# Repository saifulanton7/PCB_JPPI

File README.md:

# Progress PCB JPPI

# Rules 
   1. Untuk Setiap Pembaruan desain pcb atau skematik harus di list log pengerjaan terakhir, Nama, tanggal dan jam, serta upload ulang file yg dikerjakan
   2. Untuk melanjutkan skematik, anda bisa lihat rangkaian pada rangkaian.pdf di github ini
   3. Kalau misalnya ada kesulitan pembacaan angka gambar, spek komponen atau jalur yang aneh, bisa dilist dan kalau memungkinkan kirimkan gambar

# Log Pengerjaan
1. Saiful Anton - 12 April 2021 (22:51 WIB)
   - Selesai mengerjakan Rangkaian Power Supply dan memcicil rangkaian isolation circuit
2. Saiful Anton - 14 April 2021 (22:29 WIB)
   - Selesai mengerjakan Rangkaian Isolation circuit dengan catatan Trafo/induktor tidak tau spek sehingga dikosongin
   - Mencicil skematik forward direction gate controller
   - file skematik sudah diupdate
3. Saiful Anton - 15 April 2021 (22:45 WIB)
   - Selesai mengerjakan Rangkaian forward directional gate controller dengan catatan Trafo/induktor tidak tau spesifikasinya dan diganti dengan komponen eagle yang lain
   - file skematik sudah diupdate
3. Saiful Anton - 26 April 2021 (12:07 WIB)
   - Selesai mengerjakan Rangkaian logic circuit dan reverse directional gate controller
   - file skematik sudah diupdate
   
# Log Kesulitan
1. Saiful Anton - 12 April 2021 (22:51 WIB)
   - Kesulitan Library Trafo Power CT 18VAC, dan Trafo Power CT 9VAC pada rangkaian  
   - Tidak Tahu Spek Trafo dirangkaian isolation circuit
   - Tidak Jelasnya Nilai Resitor didekat Transistor TR1 Sampai TR8
2. Saiful Anton - 14 April 2021 (22:29 WIB)
   - Kesulitan Library Trafo/induktor tidak ada dan saya tidak tahu jenis dan speknya  
3. Saiful Anton - 15 April 2021 (22:45 WIB)
   - tidak tahunya spesifikasi Trafo/induktor isolasi

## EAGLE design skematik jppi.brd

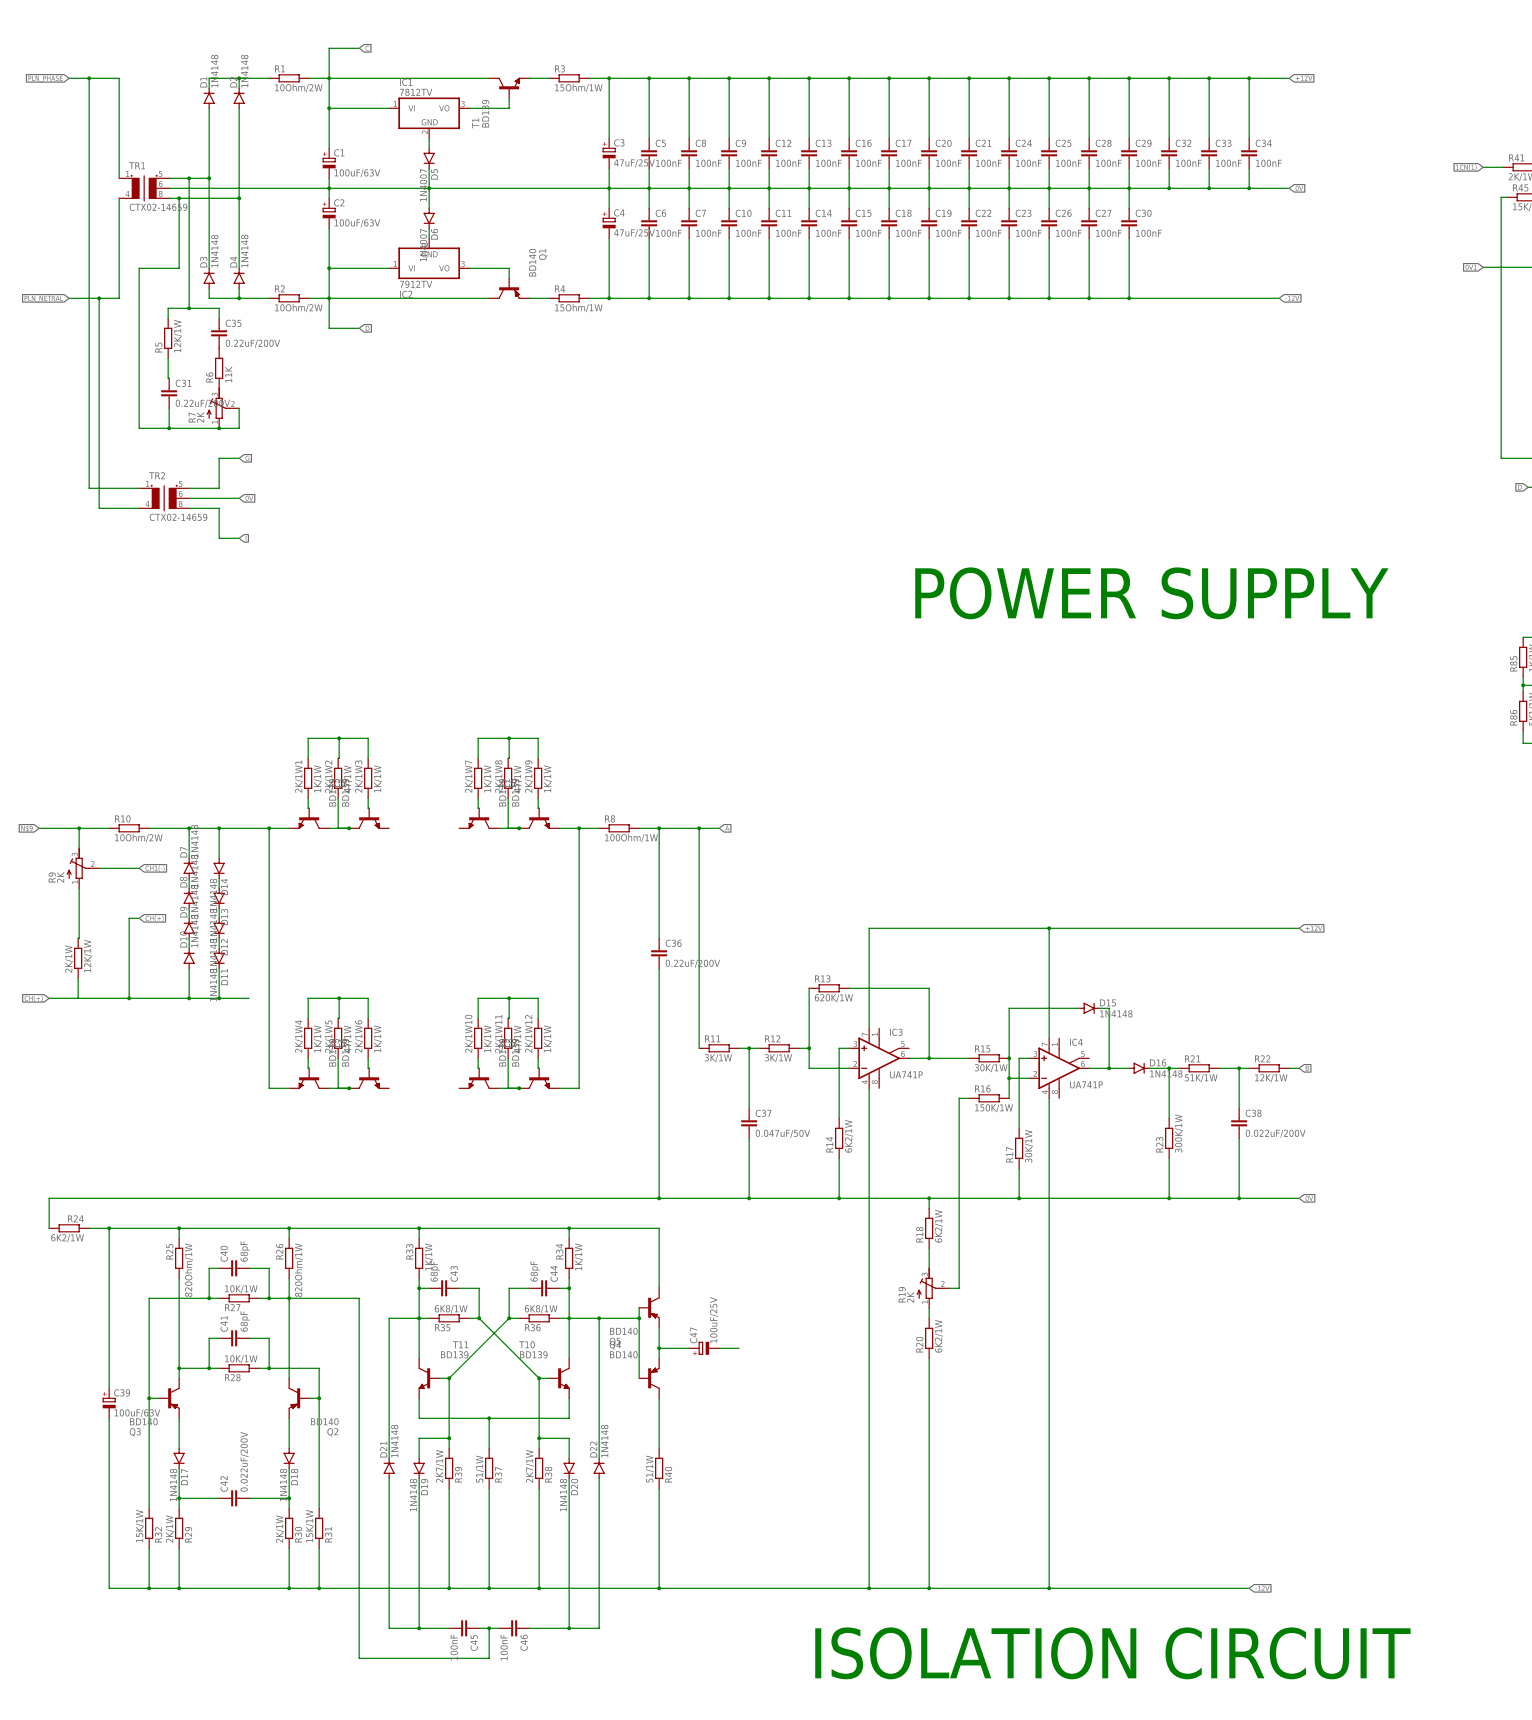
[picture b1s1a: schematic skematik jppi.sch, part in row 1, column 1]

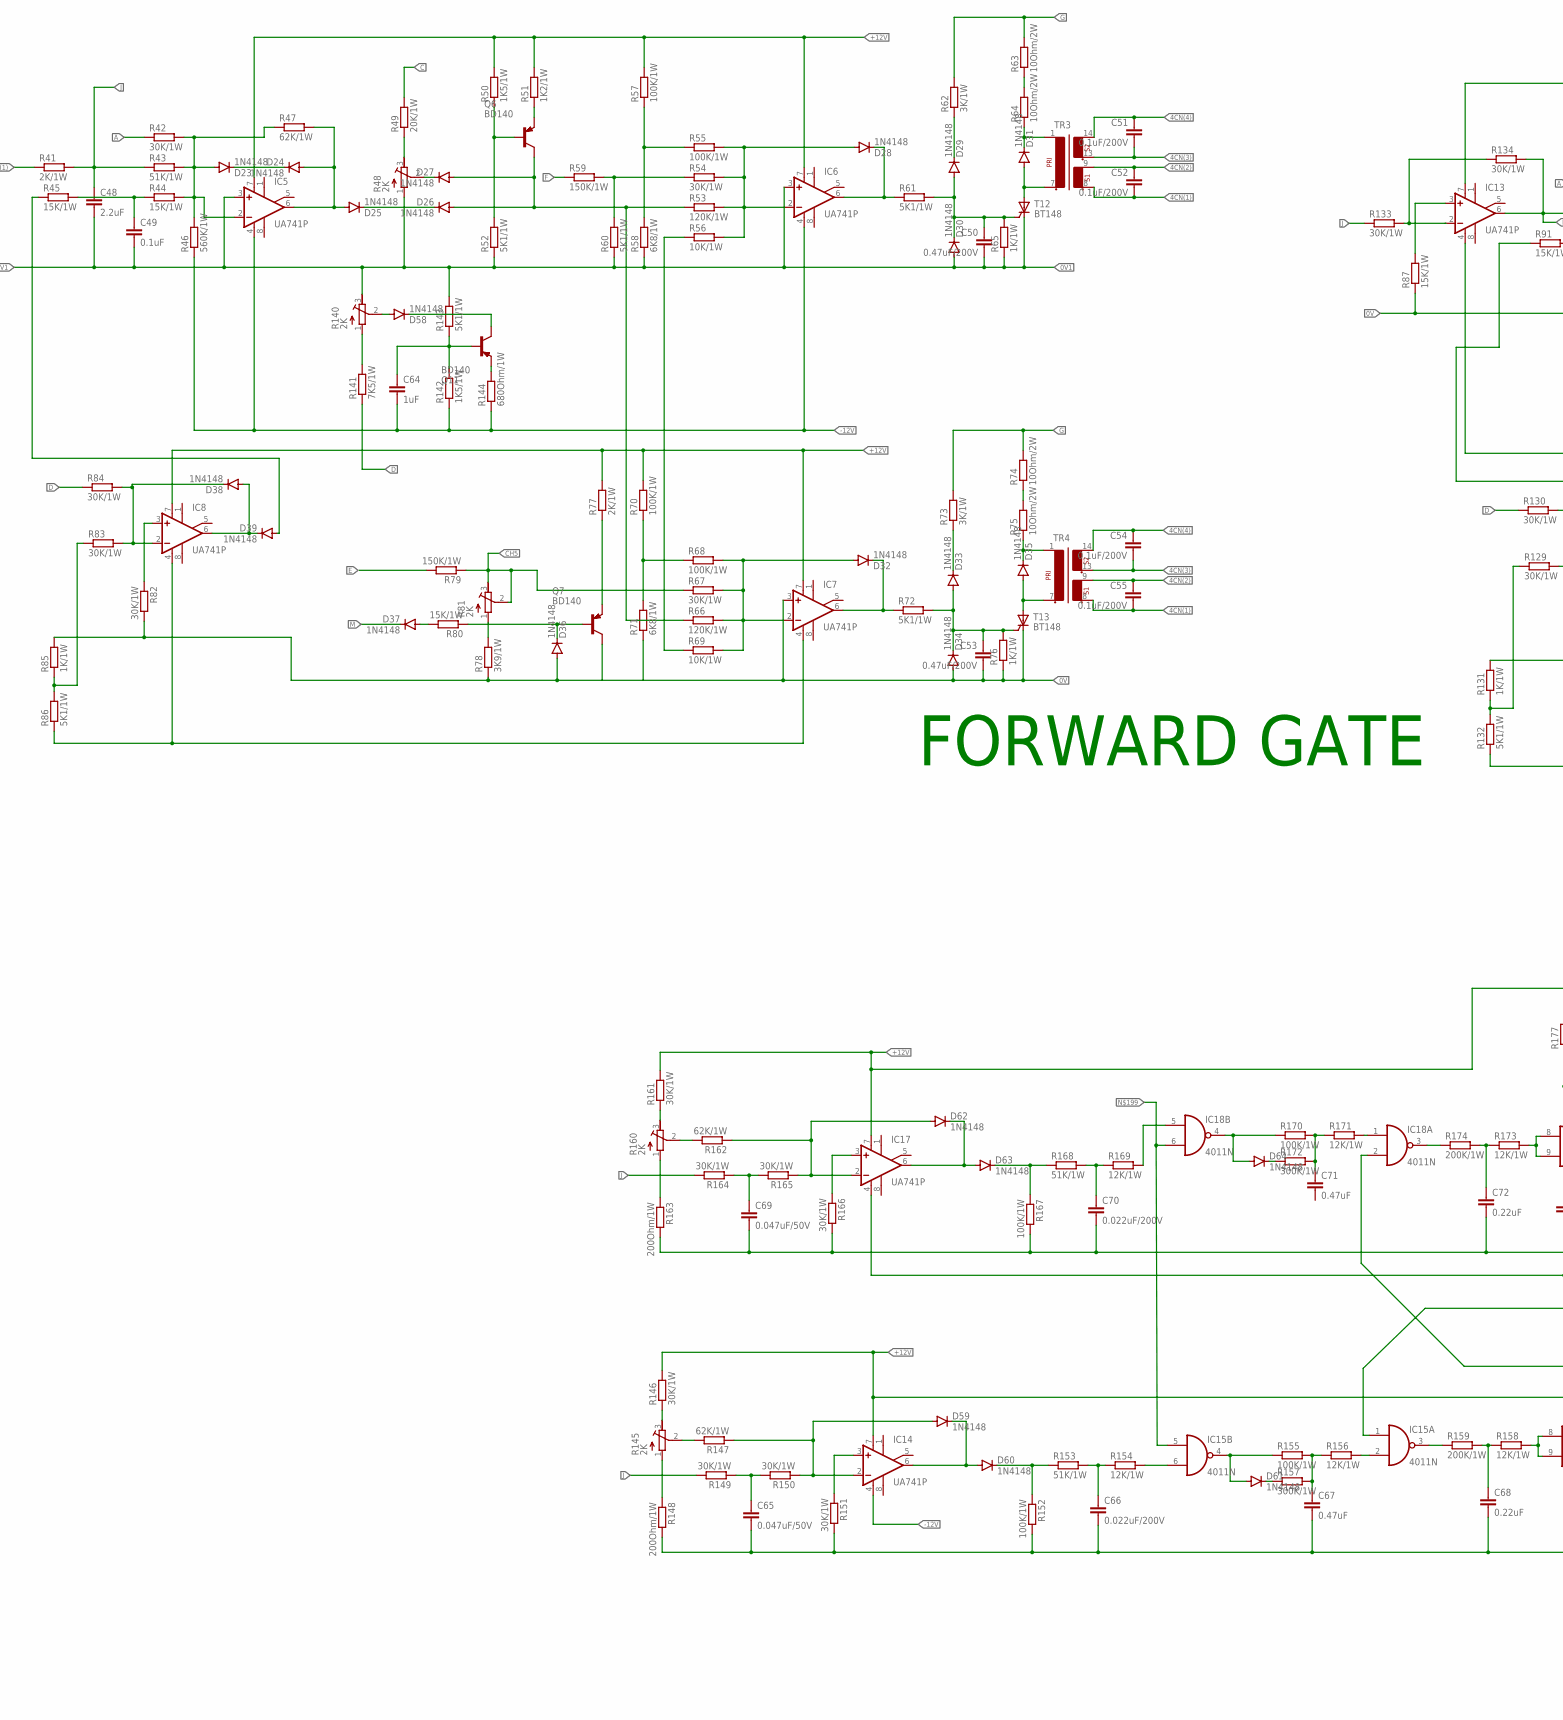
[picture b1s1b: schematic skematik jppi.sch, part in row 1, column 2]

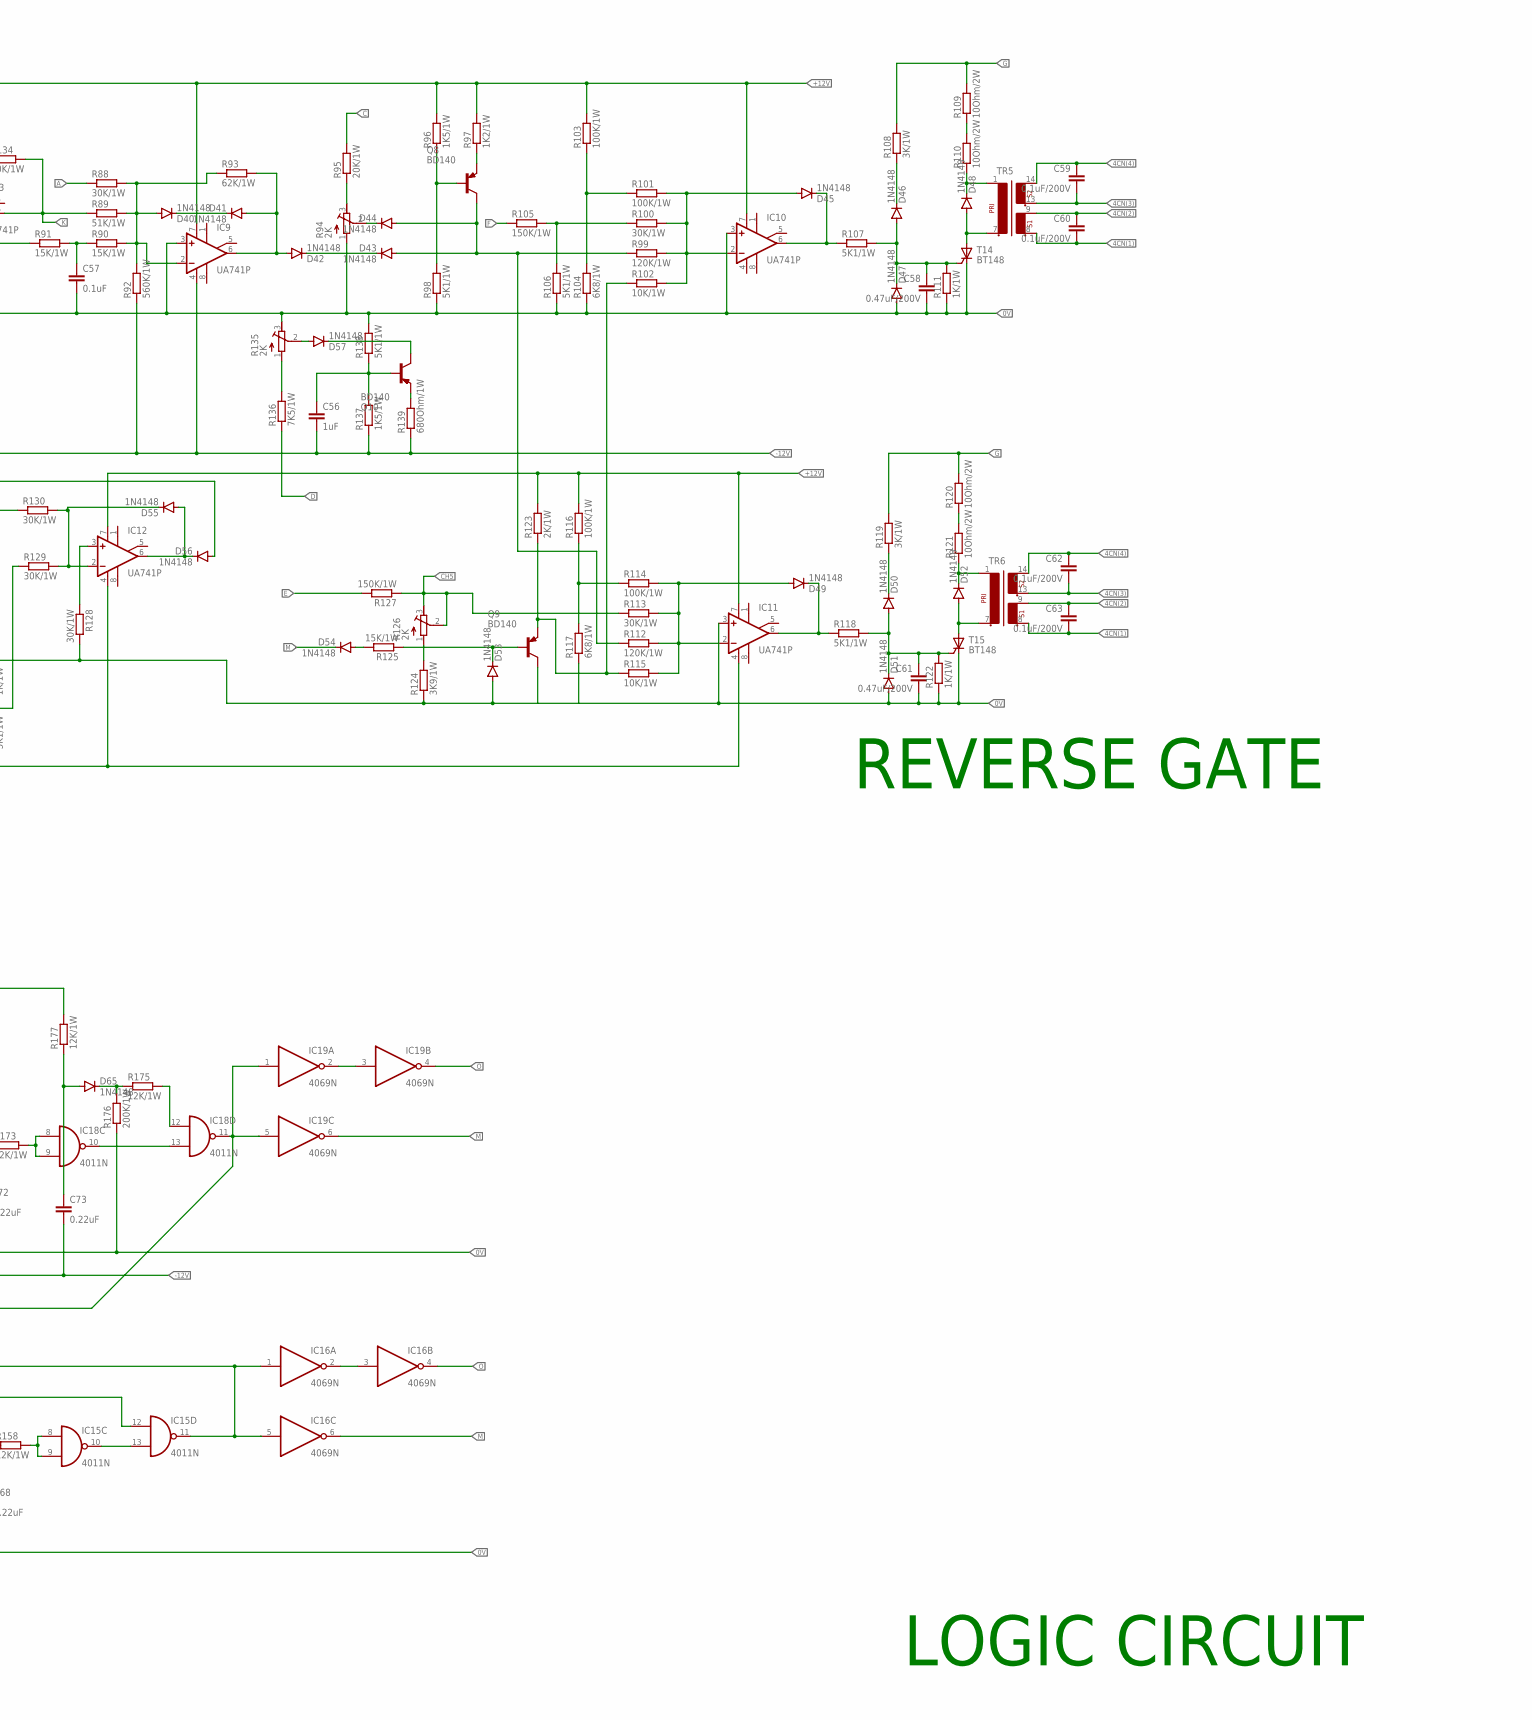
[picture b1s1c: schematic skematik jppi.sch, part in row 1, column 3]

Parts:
2K/1W: 12K/1W; 0309/12
2K/1W1, 2K/1W3, 2K/1W4, 2K/1W6, 2K/1W7, 2K/1W9, 2K/1W10, 2K/1W12: 1K/1W; 0309/12
2K/1W2, 2K/1W5, 2K/1W8, 2K/1W11: 47/1W; 0309/12
C1, C2, C39: 100uF/63V; E5-10,5
C3, C4: 47uF/25V; E5-10,5
C5, C6, C7, C8, C9, C10, C11, C12, C13, C14, C15, C16, C17, C18, C19, C20, C21, C22, C23, C24, C25, C26, C27, C28, C29, C30, C32, C33, C34, C45, C46: 100nF; C050-025X075
C31, C35, C36: 0.22uF/200V; C102-043X133
C37: 0.047uF/50V; C075-032X103
C38, C42, C66, C70: 0.022uF/200V; C102-043X133
C40, C41, C43, C44: 68pF; C050-024X044
C47: 100uF/25V; E5-10,5
C48: 2.2uF; C050-025X075
C49, C57: 0.1uF; C050-025X075
C50, C53, C58, C61: 0.47uF/200V; C102-043X133
C51, C52, C54, C55, C59, C60, C62, C63: 0.1uF/200V; C102-043X133
C56, C64: 1uF; C050-025X075
C65, C69: 0.047uF/50V; C102-043X133
C67, C71: 0.47uF; C102-043X133
C68, C72, C73: 0.22uF; C102-043X133
D1, D2, D3, D4, D7, D8, D9, D10, D11, D12, D13, D14, D15, D16, D17, D18, D19, D20, D21, D22, D23, D24, D25, D26, D27, D28, D29, D30, D31, D32, D33, D34, D35, D36, D37, D38, D39, D40, D41, D42, D43, D44, D45, D46, D47, D48, D49, D50, D51, D52, D53, D54, D55, D56, D57, D58, D59, D60, D61, D62, D63, D64, D65: 1N4148; DO41-10
D5, D6: 1N4007; DO41-10
IC1: 7812TV; TO220V
IC2: 7912TV; TO220V
IC3, IC4, IC5, IC6, IC7, IC8, IC9, IC10, IC11, IC12, IC13, IC14, IC17: UA741P; DIL08
IC15, IC18: 4011N; DIL14
IC16, IC19: 4069N; DIL14
Q1, Q2, Q3, Q4, Q5, Q6, Q7, Q8, Q9, Q10, Q11: BD140; TO126
R1, R2, R10, R63, R64, R74, R75, R109, R110, R120, R121: 10Ohm/2W; 0411/15
R3, R4: 15Ohm/1W; 0309/12
R5: 12K/1W; 0309/12
R6: 11K; 0309/12
R7, R9, R19, R48, R81, R94, R126, R135, R140, R145, R160: 2K; RTRIM3339P
R8: 100Ohm/1W; 0411/15
R11, R12, R62, R73, R108, R119: 3K/1W; 0411/15
R13: 620K/1W; 0411/15
R14, R18, R20, R24: 6K2/1W; 0411/15
R15, R17, R42, R54, R67, R82, R83, R84, R88, R100, R113, R128, R129, R130, R133, R134, R146, R149, R150, R151, R161, R164, R165, R166: 30K/1W; 0411/15
R16, R59, R79, R105, R127: 150K/1W; 0411/15
R21, R43, R89, R153, R168: 51K/1W; 0411/15
R22, R154, R156, R158, R169, R171, R173, R175, R177: 12K/1W; 0411/15
R23, R157, R172: 300K/1W; 0411/15
R25, R26: 820Ohm/1W; 0411/15
R27, R28, R56, R69, R102, R115: 10K/1W; 0411/15
R29, R30, R41, R77, R123: 2K/1W; 0411/15
R31, R32, R44, R45, R80, R87, R90, R91, R125: 15K/1W; 0411/15
R33, R34, R65, R76, R85, R111, R122, R131: 1K/1W; 0411/15
R35, R36, R58, R71, R104, R117: 6K8/1W; 0411/15
R37, R40: 51/1W; 0411/15
R38, R39: 2K7/1W; 0411/15
R46, R92: 560K/1W; 0411/15
R47, R93, R147, R162: 62K/1W; 0411/15
R49, R95: 20K/1W; 0411/15
R50, R96, R137, R142: 1K5/1W; 0411/15
R51, R97: 1K2/1W; 0411/15
R52, R60, R61, R72, R86, R98, R106, R107, R118, R132, R138, R143: 5K1/1W; 0411/15
R53, R66, R99, R112: 120K/1W; 0411/15
R55, R57, R68, R70, R101, R103, R114, R116, R152, R155, R167, R170: 100K/1W; 0411/15
R78, R124: 3K9/1W; 0411/15
R136, R141: 7K5/1W; 0411/15
R139, R144: 680Ohm/1W; 0411/15
R148, R163: 200Ohm/1W; 0411/15
R159, R174, R176: 200K/1W; 0411/15
T1, T2, T3, T4, T5, T6, T7, T8, T9, T10, T11: BD139; TO126
T12, T13, T14, T15: BT148; SOT82S
TR1, TR2: CTX02-14659
TR3, TR4, TR5, TR6: EI54-2

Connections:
0V: C1.-, C2.+, C3.-, C4.+, C5.2, C6.1, C7.1, C8.2, C9.2, C10.1, C11.1, C12.2, C13.2, C14.1, C15.1, C16.2, C17.2, C18.1, C19.1, C20.2, C21.2, C22.1, C23.1, C24.2, C25.2, C26.1, C27.1, C28.2, C29.2, C30.1, C32.2, C33.2, C34.2, C36.2, C37.2, C38.2, C53.2, C57.2, C58.2, C61.2, C65.2, C66.2, C67.2, C68.2, C69.2, C70.2, C72.2, D5.C, D6.A, D34.A, D36.A, D47.A, D51.A, D53.A, IC7.3 (+IN), IC9.3 (+IN), IC10.3 (+IN), IC11.3 (+IN), Q7.2 (C), Q9.2 (C), R14.1, R17.1, R18.2, R23.1, R24.2, R71.1, R76.1, R78.1, R82.2, R85.2, R87.1, R94.1 (A), R98.1, R104.1, R106.1, R111.1, R117.1, R122.1, R124.1, R128.2, R131.2, R135.3 (E), R138.2, R148.2, R151.2, R152.2, R163.2, R166.2, R167.2, R176.1, T13.C, T14.C, T15.C, TR1.6 (4), TR2.6 (4)
0V1: C48.2, C49.2, C50.2, D30.A, IC5.3 (+IN), IC6.3 (+IN), R48.1 (A), R52.1, R58.1, R60.1, R65.1, R140.3 (E), R143.2, T12.C
1CN(1): R41.1
4CN(1): C52.2, C55.2, C60.2, C63.2, TR3.8 (3), TR4.8 (3), TR5.8 (3), TR6.8 (3)
4CN(2): C52.1, C55.1, C60.1, C63.1, TR3.9 (4), TR4.9 (4), TR5.9 (4), TR6.9 (4)
4CN(3): C51.2, C54.2, C59.2, C62.2, TR3.13 (5), TR4.13 (5), TR5.13 (5), TR6.13 (5)
4CN(4): C51.1, C54.1, C59.1, C62.1, TR3.14 (6), TR4.14 (6), TR5.14 (6), TR6.14 (6)
+12V: C3.+, C5.1, C8.1, C9.1, C12.1, C13.1, C16.1, C17.1, C20.1, C21.1, C24.1, C25.1, C28.1, C29.1, C32.1, C33.1, C34.1, IC3.7 (V+), IC4.7 (V+), IC5.7 (V+), IC6.7 (V+), IC7.7 (V+), IC8.7 (V+), IC9.7 (V+), IC10.7 (V+), IC11.7 (V+), IC12.7 (V+), IC13.7 (V+), IC14.7 (V+), IC15.12 (I0), IC17.7 (V+), R3.2, R50.2, R51.2, R57.2, R70.2, R77.2, R96.2, R97.2, R103.2, R116.2, R123.2, R146.2, R161.2, R177.2
-12V: C4.-, C6.2, C7.2, C10.2, C11.2, C14.2, C15.2, C18.2, C19.2, C22.2, C23.2, C26.2, C27.2, C30.2, C39.-, C56.2, C64.2, C73.2, IC3.4 (V-), IC4.4 (V-), IC5.4 (V-), IC6.4 (V-), IC9.4 (V-), IC13.4 (V-), IC14.4 (V-), IC17.4 (V-), R4.2, R20.1, R29.1, R30.1, R31.1, R32.1, R37.1, R38.1, R39.1, R40.1, R46.1, R92.1, R137.1, R139.1, R142.1, R144.1
A: C36.1, R8.2, R11.1, R42.1, R88.1
B: R22.2
C: C1.+, IC1.1 (VI), R1.2, R49.2, R95.2, T1.2 (C)
CH1(-): R9.2 (S)
CH5: R67.1, R79.1, R81.2 (S), R81.3 (E), R113.1, R126.2 (S), R126.3 (E), R127.1
CH(+): 2K/1W.1, D10.A, D11.C
D: C2.-, IC2.1 (VI), Q1.2 (C), R2.2, R84.1, R130.1, R136.1, R141.1
E: R79.2, R127.2
F: R59.1, R105.1
G: R62.2, R63.2, R73.2, R74.2, R108.2, R109.2, R119.2, R120.2, TR2.5
I: TR2.8 (3)
J: C48.1, R41.2, R43.1, R133.1, R149.2, R164.2
K: IC13.6 (OUT), R89.1, R134.2
M: D37.C, D54.C, IC16.6 (O), IC19.6 (O)
unnamed: C35.1, D1.A, D3.C, R5.2, TR1.5
unnamed: C31.2, D2.A, D4.C, R7.1 (A), R7.2 (S), TR1.8 (3)
unnamed: D1.C, D2.C, R1.1
unnamed: D3.A, D4.A, R2.1
unnamed: R6.1, R7.3 (E)
unnamed: C31.1, R5.1
unnamed: 2K/1W.2, R9.1 (A)
unnamed: D6.C, IC2.2 (GND)
unnamed: R9.3 (E), R10.1
unnamed: D5.A, IC1.2 (GND)
unnamed: IC1.3 (VO), T1.3 (B)
unnamed: IC2.3 (VO), Q1.3 (B)
unnamed: Q1.1 (E), R4.1
unnamed: R3.1, T1.1 (E)
unnamed: D7.A, D8.C
unnamed: D7.C, D14.A, R10.2, T2.1 (E), T4.1 (E)
unnamed: 2K/1W2.1, T2.2 (C), T3.2 (C)
unnamed: C35.2, R6.2
unnamed: D8.A, D9.C
unnamed: D9.A, D10.C
unnamed: D11.A, D12.C
unnamed: D12.A, D13.C
unnamed: D13.A, D14.C
unnamed: 2K/1W1.1, T2.3 (B)
unnamed: 2K/1W3.1, T3.3 (B)
unnamed: 2K/1W1.2, 2K/1W2.2, 2K/1W3.2
unnamed: 2K/1W5.1, T4.2 (C), T5.2 (C)
unnamed: 2K/1W4.1, T4.3 (B)
unnamed: 2K/1W6.1, T5.3 (B)
unnamed: 2K/1W4.2, 2K/1W5.2, 2K/1W6.2
unnamed: 2K/1W8.1, T6.2 (C), T7.2 (C)
unnamed: 2K/1W7.1, T6.3 (B)
unnamed: 2K/1W9.1, T7.3 (B)
unnamed: 2K/1W7.2, 2K/1W8.2, 2K/1W9.2
unnamed: 2K/1W11.1, T8.2 (C), T9.2 (C)
unnamed: 2K/1W10.1, T8.3 (B)
unnamed: 2K/1W12.1, T9.3 (B)
unnamed: 2K/1W10.2, 2K/1W11.2, 2K/1W12.2
unnamed: R8.1, T7.1 (E), T9.1 (E)
unnamed: R63.1, R64.2
unnamed: R19.1 (A), R20.2
unnamed: C37.1, R11.2, R12.1
unnamed: IC3.2 (-IN), R12.2, R13.1
unnamed: IC3.6 (OUT), R13.2, R15.1
unnamed: IC3.3 (+IN), R14.2
unnamed: IC4.3 (+IN), R17.2
unnamed: R18.1, R19.3 (E)
unnamed: R16.1, R19.2 (S)
unnamed: D15.C, D16.A, IC4.6 (OUT)
unnamed: C39.+, Q5.2 (C), R24.1, R25.1, R26.1, R33.1, R34.1
unnamed: D16.C, R21.1, R23.2
unnamed: C38.1, R21.2, R22.1
unnamed: C41.1, Q3.2 (C), R25.2, R28.1
unnamed: C47.+, Q4.1 (E), Q5.1 (E)
unnamed: C41.2, Q2.3 (B), R28.2, R31.2
unnamed: C40.1, Q3.3 (B), R27.1, R32.2
unnamed: D17.A, Q3.1 (E)
unnamed: D18.A, Q2.1 (E)
unnamed: C42.1, D17.C, R29.2
unnamed: C42.2, D18.C, R30.2
unnamed: C43.2, D21.C, R33.2, R35.1, T11.2 (C)
unnamed: C40.2, C45.1, C46.2, Q2.2 (C), R26.2, R27.2
unnamed: C43.1, D20.A, R35.2, R38.2, T10.3 (B)
unnamed: C44.2, D19.A, R36.1, R39.2, T11.3 (B)
unnamed: R37.2, T10.1 (E), T11.1 (E)
unnamed: C46.1, D20.C, D22.A
unnamed: C44.1, D22.C, Q4.3 (B), Q5.3 (B), R34.2, R36.2, T10.2 (C)
unnamed: C45.2, D19.C, D21.A
unnamed: D23.A, IC5.2 (-IN), R42.2, R43.2, R44.2, R46.2, R47.1
unnamed: Q4.2 (C), R40.2
unnamed: C49.1, R44.1, R45.2
unnamed: R56.1, R69.1
unnamed: D15.A, IC4.2 (-IN), R15.2, R16.2
unnamed: D24.A, D25.A, IC5.6 (OUT), R47.2
unnamed: D25.C, D26.C
unnamed: D23.C, D24.C
unnamed: D27.C, R48.2 (S)
unnamed: R48.3 (E), R49.1
unnamed: Q6.1 (E), R51.1
unnamed: Q6.3 (B), R50.1, R52.2
unnamed: D26.A, D27.A, Q6.2 (C), R53.1, R66.1
unnamed: D28.A, IC6.2 (-IN), R53.2, R54.2, R55.2, R56.2
unnamed: R55.1, R57.1, R58.2
unnamed: R54.1, R59.2, R60.2
unnamed: D28.C, IC6.6 (OUT), R61.1
unnamed: C50.1, D29.A, D30.C, R61.2, R65.2, T12.G
unnamed: D29.C, R62.1
unnamed: D31.C, R64.1, TR3.1
unnamed: D31.A, T12.A, TR3.7 (2)
unnamed: D32.A, IC7.2 (-IN), R66.2, R67.2, R68.2, R69.2
unnamed: R68.1, R70.1, R71.2
unnamed: R78.2, R81.1 (A)
unnamed: D32.C, IC7.6 (OUT), R72.1
unnamed: C53.1, D33.A, D34.C, R72.2, R76.2, T13.G
unnamed: D33.C, R73.1
unnamed: R74.1, R75.2
unnamed: D35.C, R75.1, TR4.1
unnamed: D35.A, T13.A, TR4.7 (2)
unnamed: Q7.1 (E), R77.1
unnamed: D36.C, Q7.3 (B), R80.1
unnamed: IC7.4 (V-), IC8.4 (V-), R86.1
unnamed: R83.1, R85.1, R86.2
unnamed: D37.A, R80.2
unnamed: D38.A, D39.C, IC8.6 (OUT)
unnamed: IC8.3 (+IN), R82.1
unnamed: D38.C, IC8.2 (-IN), R83.2, R84.2
unnamed: D39.A, R45.1
unnamed: D40.A, IC9.2 (-IN), R88.2, R89.2, R90.2, R92.2, R93.1
unnamed: C57.1, R90.1, R91.2
unnamed: D41.A, D42.A, IC9.6 (OUT), R93.2
unnamed: D40.C, D41.C
unnamed: D42.C, D43.C
unnamed: D44.C, R94.2 (S)
unnamed: R94.3 (E), R95.1
unnamed: Q8.1 (E), R97.1
unnamed: Q8.3 (B), R96.1, R98.2
unnamed: D43.A, D44.A, Q8.2 (C), R99.1, R112.1
unnamed: D45.A, IC10.2 (-IN), R99.2, R100.2, R101.2, R102.2
unnamed: R101.1, R103.1, R104.2
unnamed: R100.1, R105.2, R106.2
unnamed: D45.C, IC10.6 (OUT), R107.1
unnamed: C58.1, D46.A, D47.C, R107.2, R111.2, T14.G
unnamed: D46.C, R108.1
unnamed: R109.1, R110.2
unnamed: D48.C, R110.1, TR5.1
unnamed: D48.A, T14.A, TR5.7 (2)
unnamed: D57.C, Q10.2 (C)
unnamed: C56.1, Q10.3 (B), R137.2, R138.1
unnamed: D49.A, IC11.2 (-IN), R112.2, R113.2, R114.2, R115.2
unnamed: R114.1, R116.1, R117.2
unnamed: D49.C, IC11.6 (OUT), R118.1
unnamed: C61.1, D50.A, D51.C, R118.2, R122.2, T15.G
unnamed: D50.C, R119.1
unnamed: R120.1, R121.2
unnamed: Q9.1 (E), R102.1, R115.1, R123.1
unnamed: D52.C, R121.1, TR6.1
unnamed: D52.A, T15.A, TR6.7 (2)
unnamed: D58.A, R140.2 (S)
unnamed: R124.2, R126.1 (A)
unnamed: D58.C, Q11.2 (C)
unnamed: D53.C, Q9.3 (B), R125.1
unnamed: D54.A, R125.2
unnamed: IC11.4 (V-), IC12.4 (V-), R132.1
unnamed: R129.1, R131.1, R132.2
unnamed: D55.A, D56.C, IC12.6 (OUT)
unnamed: D55.C, IC12.2 (-IN), R129.2, R130.2
unnamed: IC13.3 (+IN), R87.2
unnamed: IC13.2 (-IN), R133.2, R134.1
unnamed: D57.A, R135.2 (S)
unnamed: Q10.1 (E), R139.2
unnamed: IC12.3 (+IN), R128.1
unnamed: D56.A, R91.1
unnamed: C64.1, Q11.3 (B), R142.2, R143.1
unnamed: R135.1 (A), R136.2
unnamed: R140.1 (A), R141.2
unnamed: Q11.1 (E), R144.2
unnamed: R145.3 (E), R146.1
unnamed: R145.1 (A), R148.1
unnamed: R145.2 (S), R147.2
unnamed: C65.1, R149.1, R150.2
unnamed: R160.3 (E), R161.1
unnamed: D59.A, IC14.2 (-IN), R147.1, R150.1
unnamed: IC14.3 (+IN), R151.1
unnamed: D59.C, D60.A, IC14.6 (OUT)
unnamed: D60.C, R152.1, R153.1
unnamed: C66.1, R153.2, R154.1
unnamed: IC15.11 (O), IC16.1 (I), IC16.5 (I), IC18.2 (I1)
unnamed: IC16.2 (O), IC16.3 (I)
unnamed: IC15.6 (I1), R154.2
unnamed: R160.1 (A), R163.1
unnamed: IC15.10 (O), IC15.13 (I1)
unnamed: IC15.8 (I0), IC15.9 (I1), R158.2
unnamed: C67.1, R155.2, R156.1, R157.2
unnamed: D61.A, IC15.4 (O), R155.1
unnamed: D61.C, R157.1
unnamed: IC15.3 (O), R159.1
unnamed: C68.1, R158.1, R159.2
unnamed: IC15.2 (I1), R156.2
unnamed: R160.2 (S), R162.2
unnamed: C69.1, R164.1, R165.2
unnamed: D62.A, IC17.2 (-IN), R162.1, R165.1
unnamed: IC17.3 (+IN), R166.1
unnamed: D62.C, D63.A, IC17.6 (OUT)
unnamed: D63.C, R167.1, R168.1
unnamed: C70.1, R168.2, R169.1
unnamed: IC18.12 (I0), R175.2
unnamed: IC19.2 (O), IC19.3 (I)
unnamed: IC18.10 (O), IC18.13 (I1)
unnamed: IC18.8 (I0), IC18.9 (I1), R173.2
unnamed: C71.1, R170.2, R171.1, R172.2
unnamed: D64.A, IC18.4 (O), R170.1
unnamed: D64.C, R172.1
unnamed: IC18.3 (O), R174.1
unnamed: C72.1, R173.1, R174.2
unnamed: IC18.5 (I0), R169.2
unnamed: IC18.1 (I0), R171.2
unnamed: D65.C, R175.1, R176.2
unnamed: IC15.5 (I0), IC18.6 (I1)
unnamed: IC15.1 (I0), IC18.11 (O), IC19.1 (I), IC19.5 (I)
unnamed: C73.1, D65.A, R177.1
O: IC16.4 (O), IC19.4 (O)
PLN_NETRAL: TR1.4 (2), TR2.4 (2)
PLN_PHASE: TR1.1, TR2.1
V-: IC10.4 (V-)
VDD: IC15.14 (VDD), IC16.14 (VDD), IC18.14 (VDD), IC19.14 (VDD)
VSS: IC15.7 (VSS), IC16.7 (VSS), IC18.7 (VSS), IC19.7 (VSS)

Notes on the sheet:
POWER SUPPLY
ISOLATION CIRCUIT
FORWARD GATE
REVERSE GATE
LOGIC CIRCUIT

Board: 2 copper layers, 379 parts (0 on the bottom side), 224 nets, no tracks yet.

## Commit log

2021-04-12 Add files via upload
    masalah :
    1. cek dan tolong pastiin resistor itu nilainya 47Ohm atau bukan
    2. Spek trafo yang dilingkari menggunakan apa
    3. linenya kemana
